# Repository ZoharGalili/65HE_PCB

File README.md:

# 65HE_PCB

this is a 65% hall effect keyboard pcb running [libhmk](https://github.com/peppapighs/libhmk) firmware.

## Board Renders

## Features

- all the usual features of an HE keyboard listed in the [libhmk](https://github.com/peppapighs/libhmk) repo.
- multilayout support (7u/6.25u spacebar, split backspace, stepped caps).
- bakeneko 65 combined with ai03 vega board outline supports gummy o-ring mount.
- at32f405 microcontroller enables 8khz polling rate.
- uses 4 of the ai03 vega outer plate screws.

## Layout

### big thanks to peppapighs 

I pretty much coppied the schematic design of the [HE60](https://github.com/peppapighs/HE60) xD

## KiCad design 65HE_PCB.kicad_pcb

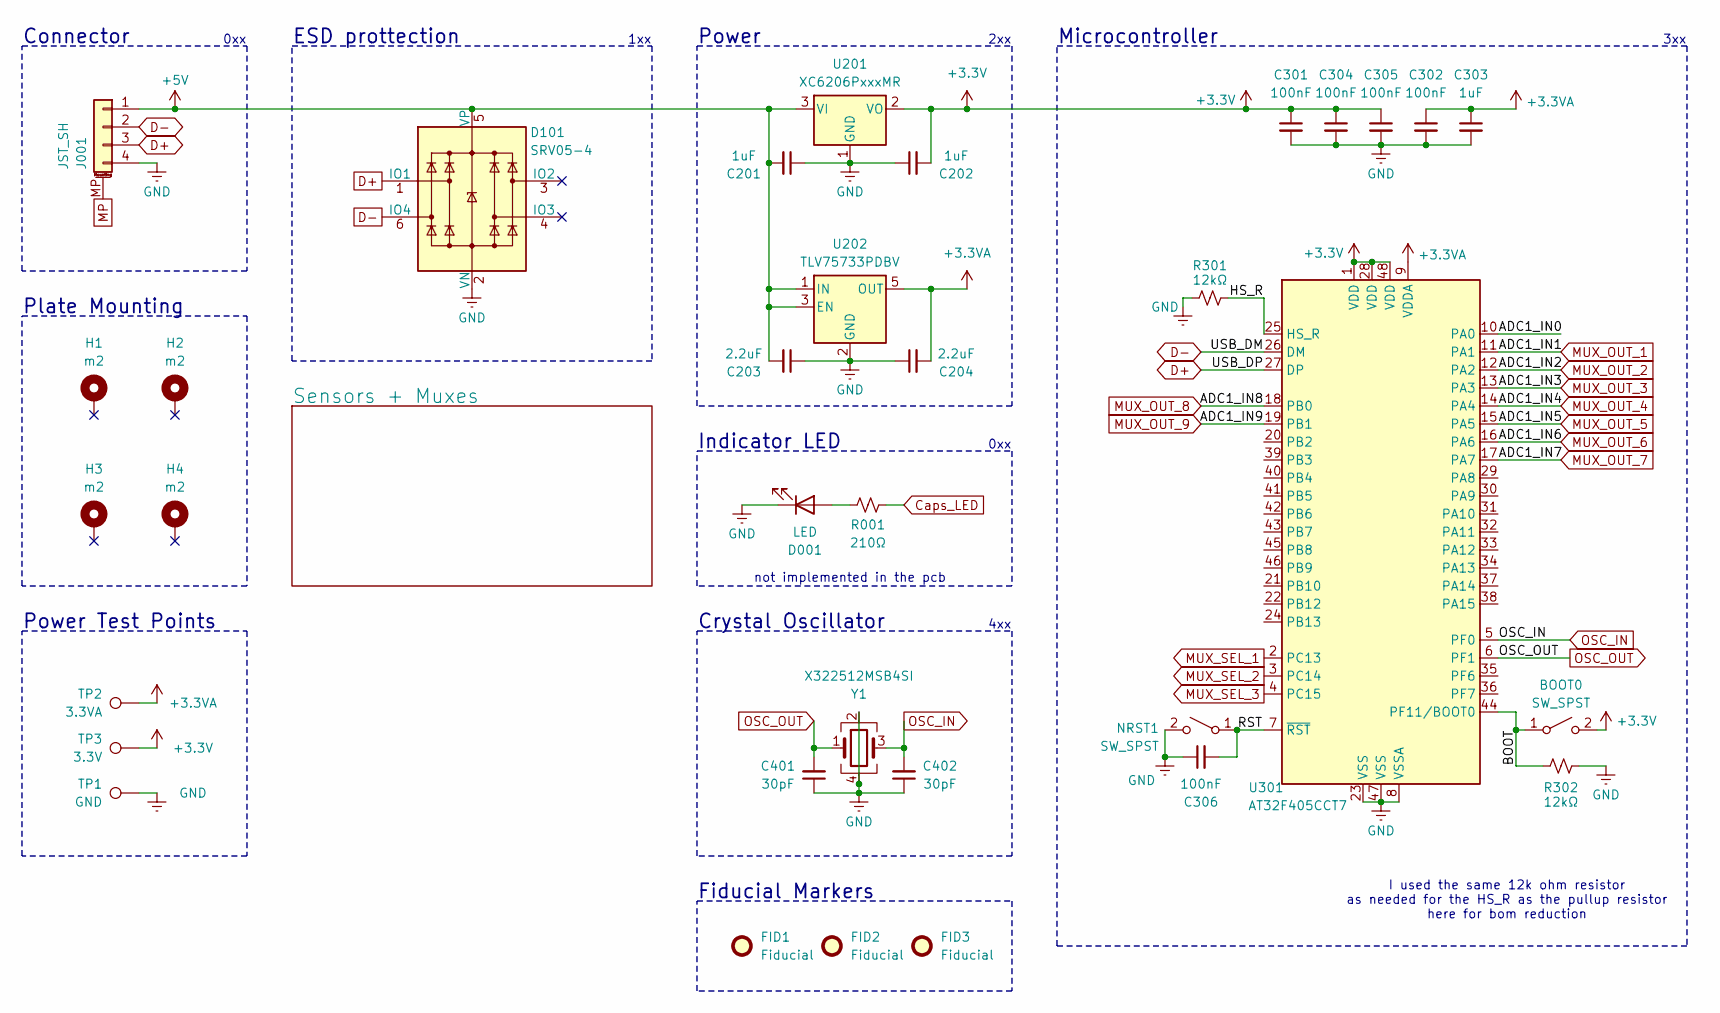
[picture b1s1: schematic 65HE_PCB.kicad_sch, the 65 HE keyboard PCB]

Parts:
BOOT0: SW_SPST; SW_SPST_SKQG_WithStem
C201, C202, C303: 1uF; C_1206_3216Metric
C203, C204: 2.2uF; C_1206_3216Metric
C301, C302, C304, C305, C306: 100nF; C_0805_2012Metric
C401, C402: 30pF; C_0603_1608Metric
D001: LED; LED_1206_3216Metric_ReverseMount_Hole1.8x2.4mm
D101: SRV05-4; SOT-23-6-routable
FID1, FID2, FID3: Fiducial; Fiducial_1mm_Mask2mm
H1, H2, H3, H4: m2; MountingHole_2.2mm_M2_Pad
J001: JST_SH; JST_SH_SM04B-SRSS-TB_1x04-1MP_P1.00mm_Horizontal
NRST1: SW_SPST; SW_SPST_SKQG_WithStem
R001: 210Ω; R_0805_2012Metric; LCSC C5357171
R301, R302: 12kΩ; R_0805_2012Metric
TP1: GND; TestPoint_Pad_2.0x2.0mm
TP2: 3.3VA; TestPoint_Pad_D2.0mm
TP3: 3.3V; TestPoint_Pad_D2.0mm
U201: XC6206PxxxMR; SOT-23-3
U202: TLV75733PDBV; SOT-23-5
U301: AT32F405CCT7; LQFP-48_7x7mm_P0.5mm
Y1: X322512MSB4SI; Crystal_SMD_3225-4Pin_3.2x2.5mm

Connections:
+3.3V: BOOT0.2 (B), C202.2, C301.1, C304.1, C305.1, TP3.1, U201.2 (VO), U301.1 (VDD), U301.28 (VDD), U301.48 (VDD)
+3.3VA: C204.2, C302.1, C303.1, TP2.1, U202.5 (OUT), U301.9 (VDDA); also elsewhere on the board
+5V: C201.2, C203.2, D101.5 (VP), J001.1, U201.3 (VI), U202.1 (IN), U202.3 (EN)
/ADC1_IN0: U301.10 (PA0)
/BOOT: BOOT0.1 (A), R302.2, U301.44 (PF11/BOOT0)
/HS_R: R301.1, U301.25 (HS_R)
/RST: C306.2, NRST1.1 (A), U301.7 (~RST)
D+: D101.1 (IO1), J001.3, U301.27 (DP)
D-: D101.6 (IO4), J001.2, U301.26 (DM)
GND: C201.1, C202.1, C203.1, C204.1, C301.2, C302.2, C303.2, C304.2, C305.2, C306.1, C401.1, C402.1, D001.1 (K), D101.2 (VN), J001.4, NRST1.2 (B), R301.2, R302.1, TP1.1, U201.1 (GND), U202.2 (GND), U301.8 (VSSA), U301.23 (VSS), U301.47 (VSS), Y1.2, Y1.4; also elsewhere on the board
MP: J001.MP (MountPin)
MUX_OUT_1: U301.11 (PA1); also elsewhere on the board
MUX_OUT_2: U301.12 (PA2); also elsewhere on the board
MUX_OUT_3: U301.13 (PA3); also elsewhere on the board
MUX_OUT_4: U301.14 (PA4); also elsewhere on the board
MUX_OUT_5: U301.15 (PA5); also elsewhere on the board
MUX_OUT_6: U301.16 (PA6); also elsewhere on the board
MUX_OUT_7: U301.17 (PA7); also elsewhere on the board
MUX_OUT_8: U301.18 (PB0); also elsewhere on the board
MUX_OUT_9: U301.19 (PB1); also elsewhere on the board
MUX_SEL_1: U301.2 (PC13); also elsewhere on the board
MUX_SEL_2: U301.3 (PC14); also elsewhere on the board
MUX_SEL_3: U301.4 (PC15); also elsewhere on the board
unnamed: D001.2 (A), R001.1
OSC_IN: C402.2, U301.5 (PF0), Y1.3
OSC_OUT: C401.2, U301.6 (PF1), Y1.1

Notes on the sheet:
Connector
Power Test Points
1xx
2xx
0xx
Plate Mounting
Fiducial Markers
ESD prottection
3xx
Power
not implemented in the pcb
Microcontroller
4xx
I used the same 12k ohm resistor as needed for the HS_R as the pullup resistor here for bom reduction
Indicator LED
Crystal Oscillator

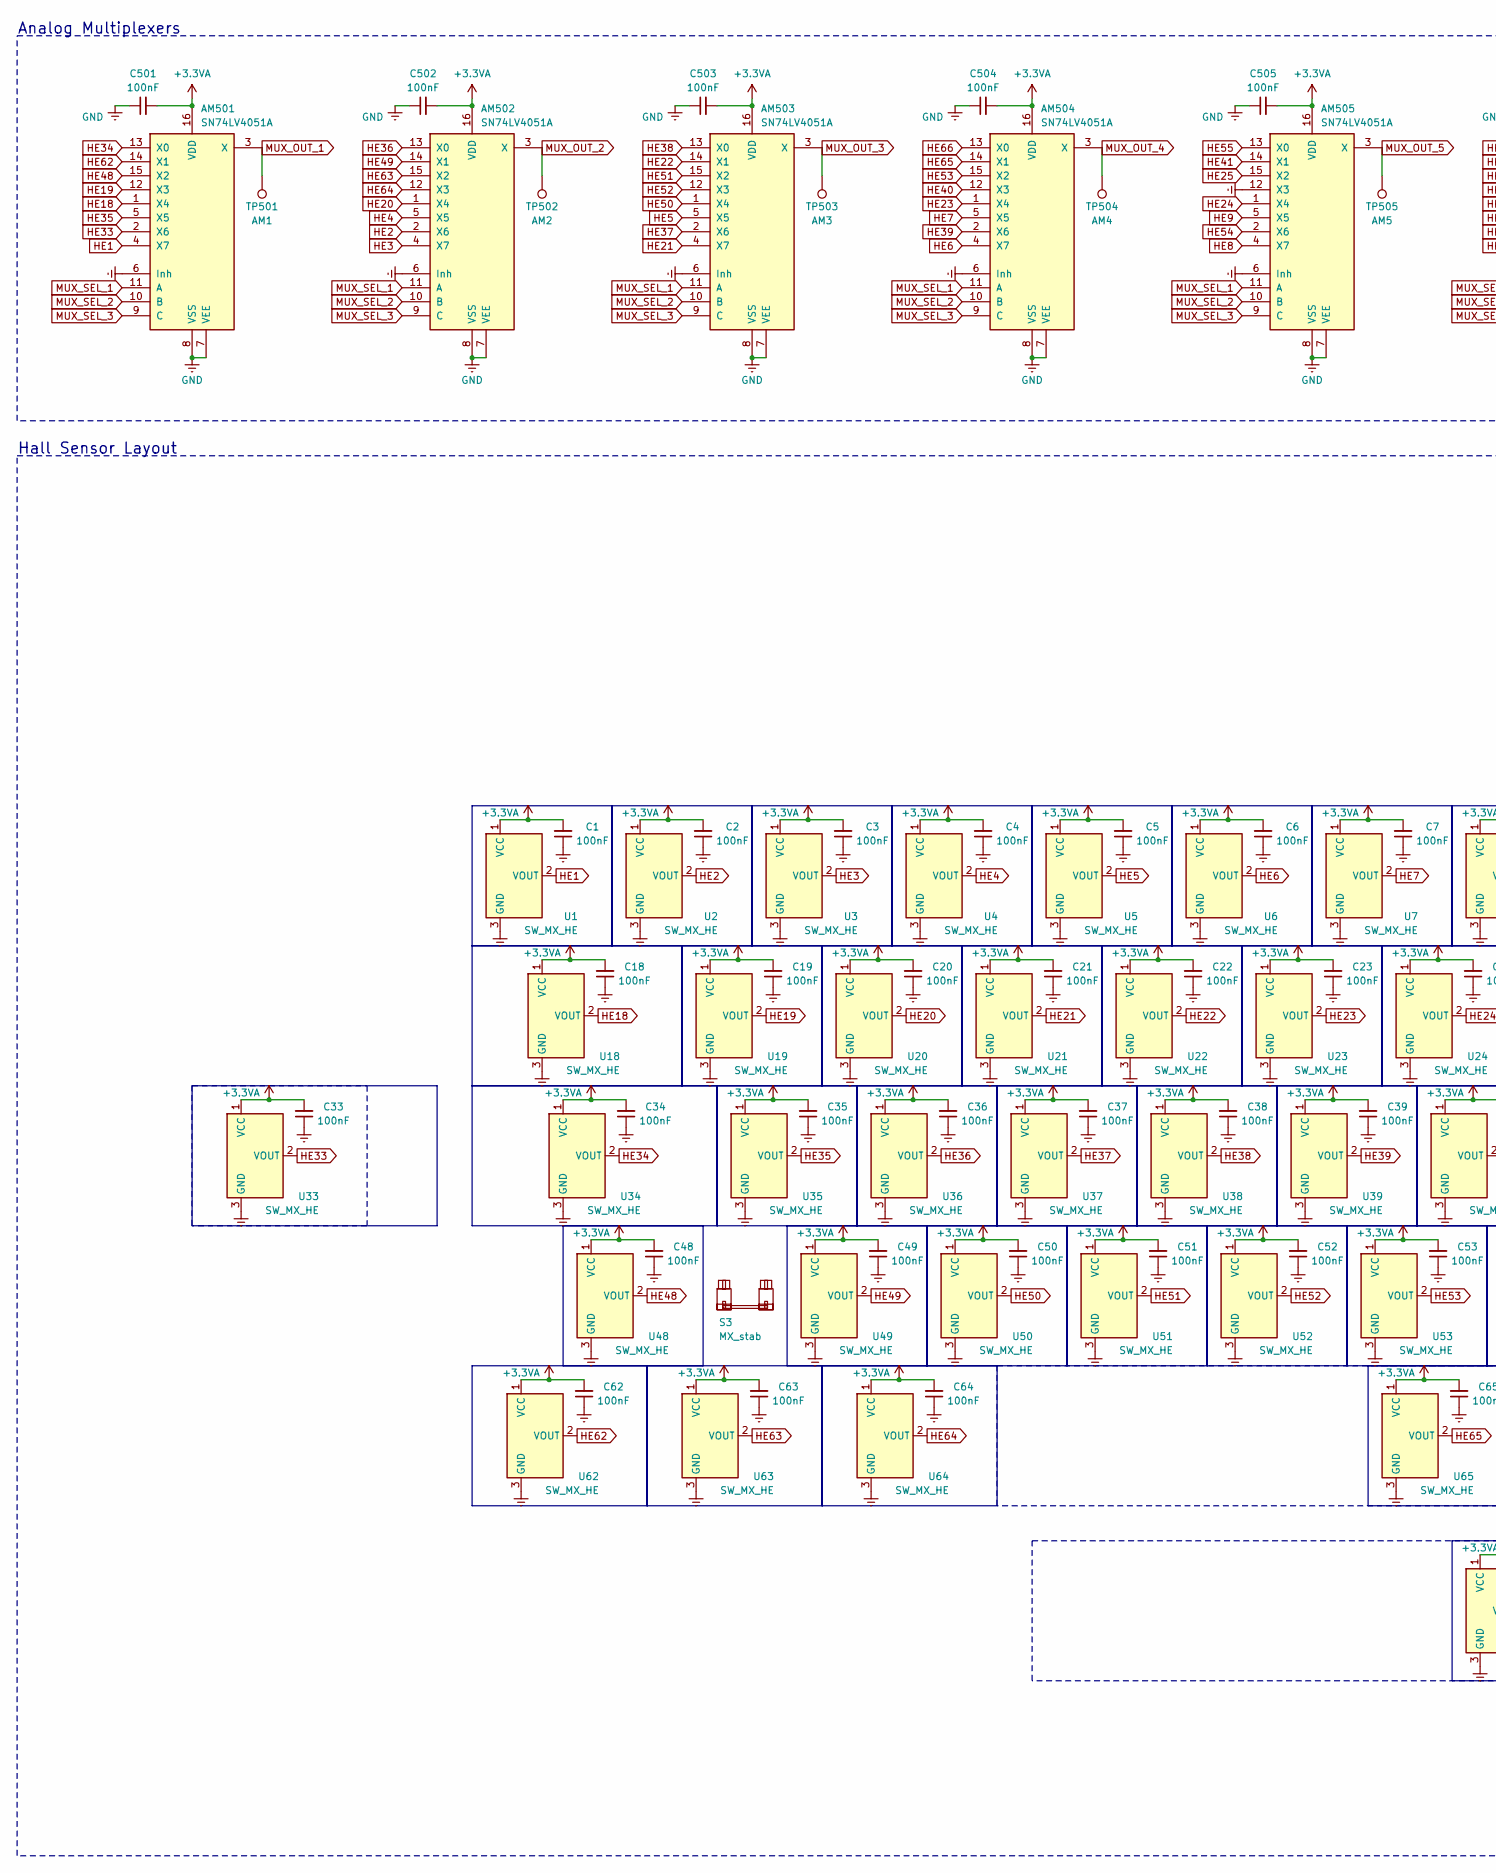
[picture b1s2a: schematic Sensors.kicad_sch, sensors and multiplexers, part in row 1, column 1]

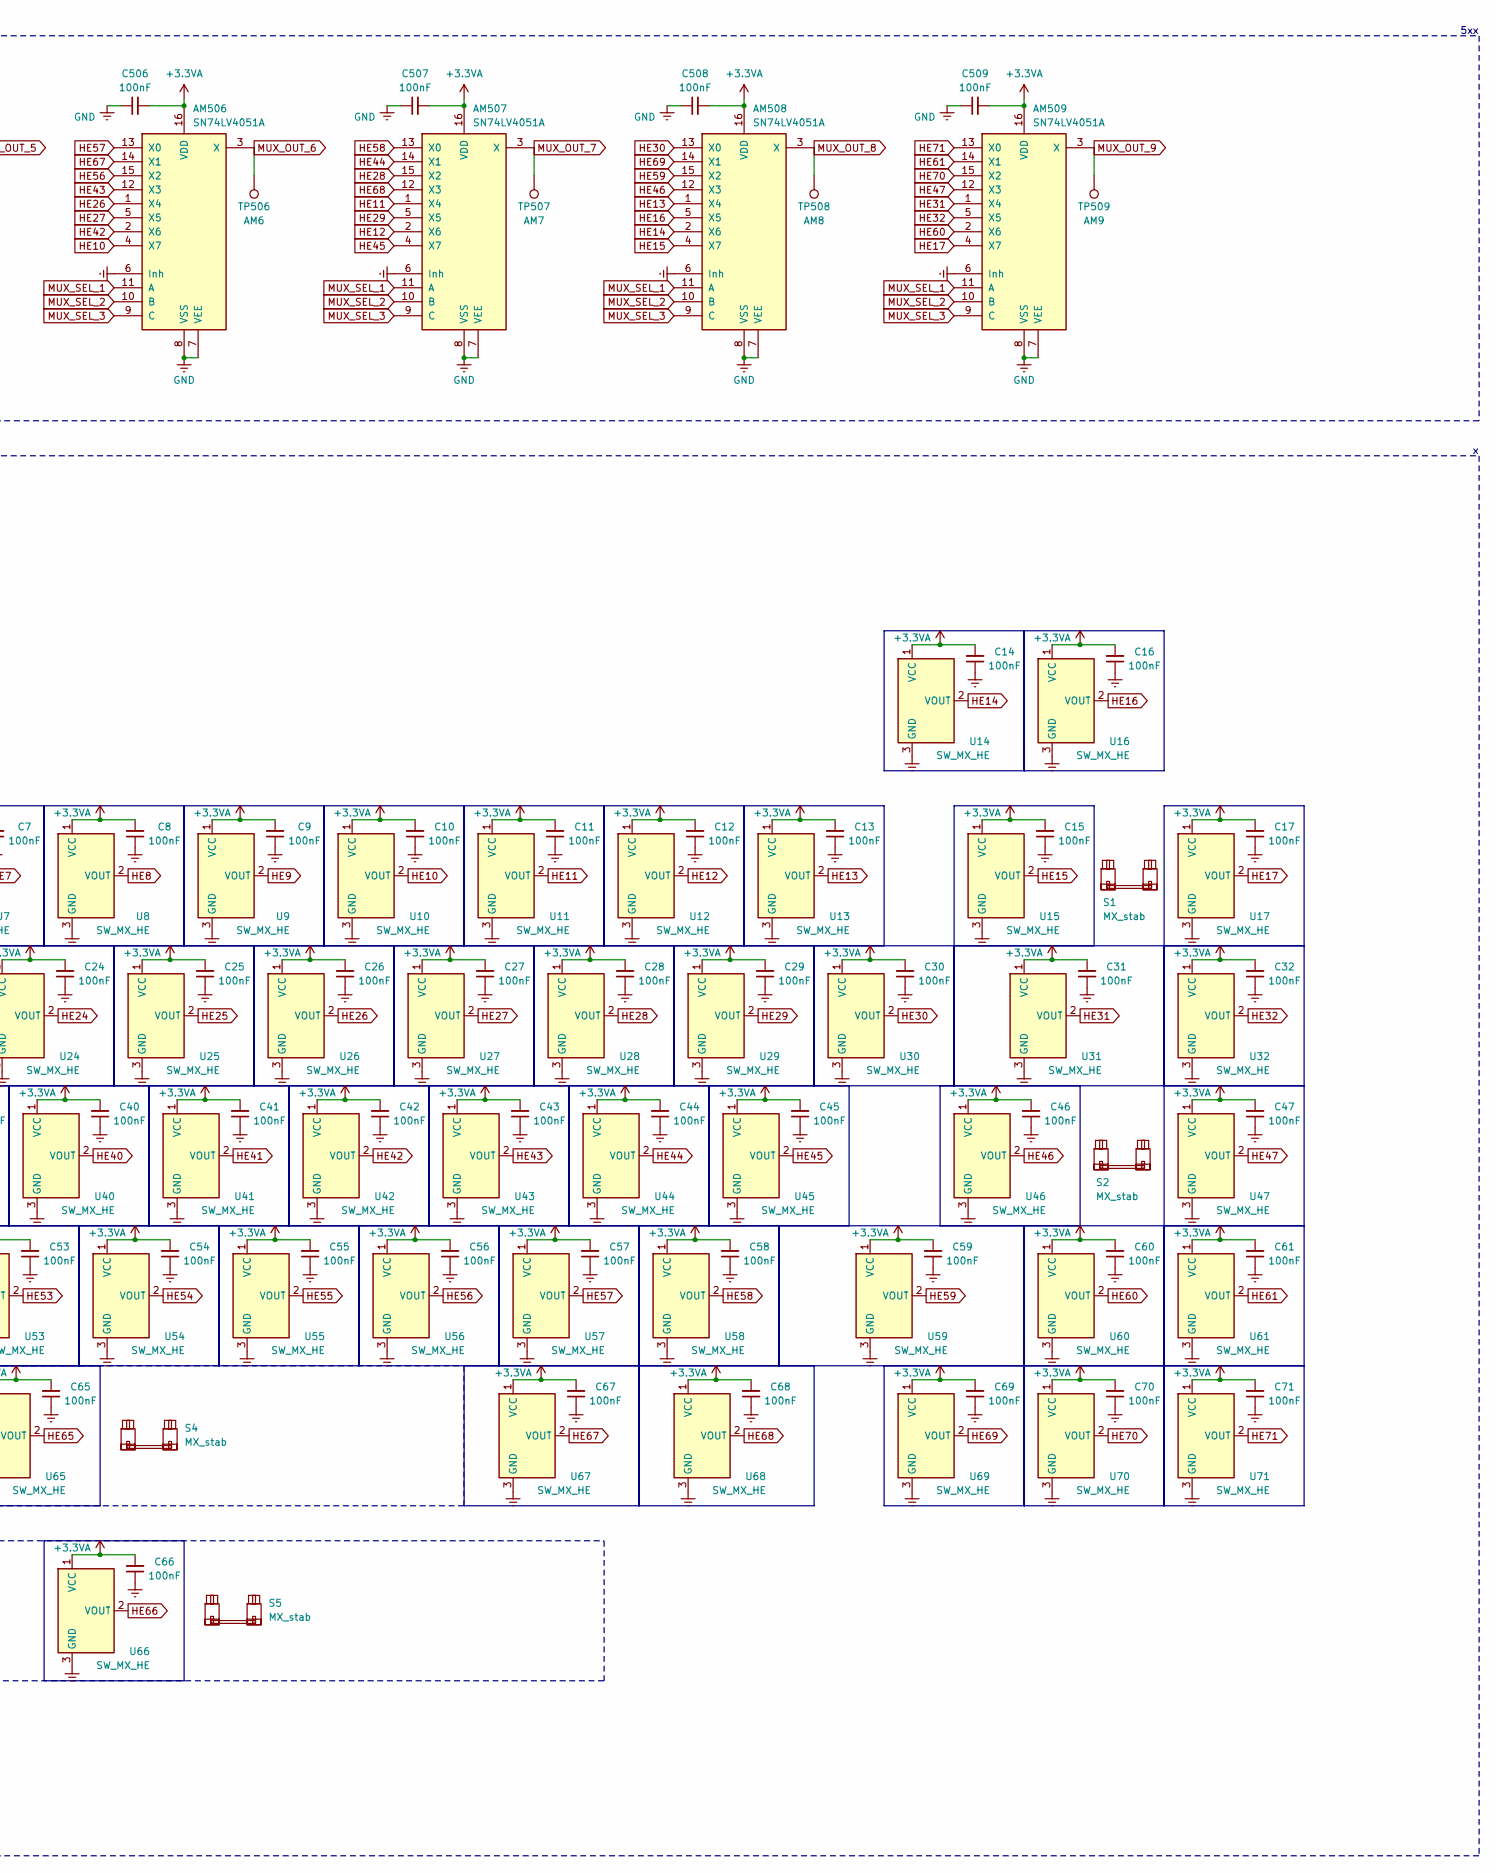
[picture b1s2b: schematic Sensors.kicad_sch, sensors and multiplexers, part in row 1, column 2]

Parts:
AM501, AM502, AM503, AM504, AM505, AM506, AM507, AM508, AM509: SN74LV4051A; TSSOP-16_4.4x5mm_P0.65mm
C1, C2, C3, C4, C5, C6, C7, C8, C9, C10, C11, C12, C13, C14, C15, C16, C17, C18, C19, C20, C21, C22, C23, C24, C25, C26, C27, C28, C29, C30, C31, C32, C33, C34, C35, C36, C37, C38, C39, C40, C41, C42, C43, C44, C45, C46, C47, C48, C49, C50, C51, C52, C53, C54, C55, C56, C57, C58, C59, C60, C61, C62, C63, C64, C65, C66, C67, C68, C69, C70, C71, C501, C502, C503, C504, C505, C506, C507, C508, C509: 100nF; C_0805_2012Metric
S1: MX_stab; STAB_MX_P_2u
S2, S3: MX_stab; STAB_MX_P_2.25u
S4: MX_stab; STAB_MX_P_6.25u
S5: MX_stab; STAB_MX_P_7u
TP501: AM1; TestPoint_Pad_D2.0mm
TP502: AM2; TestPoint_Pad_D2.0mm
TP503: AM3; TestPoint_Pad_D2.0mm
TP504: AM4; TestPoint_Pad_D2.0mm
TP505: AM5; TestPoint_Pad_D2.0mm
TP506: AM6; TestPoint_Pad_D2.0mm
TP507: AM7; TestPoint_Pad_D2.0mm
TP508: AM8; TestPoint_Pad_D2.0mm
TP509: AM9; TestPoint_Pad_D2.0mm
U1, U2, U3, U4, U5, U6, U7, U8, U9, U10, U11, U12, U13, U14, U15, U16, U17, U18, U19, U20, U21, U22, U23, U24, U25, U26, U27, U28, U29, U30, U31, U32, U34, U35, U36, U37, U38, U39, U40, U41, U42, U43, U44, U45, U46, U47, U48, U49, U50, U51, U52, U53, U54, U55, U56, U57, U58, U59, U60, U61, U65, U66, U67, U69, U70, U71: SW_MX_HE; SW_MX_HE_90deg_1u
U33: SW_MX_HE; SW_MX_HE_90deg_1.75u_STP_1.25
U62, U63, U64, U68: SW_MX_HE; SW_MX_HE_90deg_1_8u

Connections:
+3.3VA: AM501.16 (VDD), AM502.16 (VDD), AM503.16 (VDD), AM504.16 (VDD), AM505.16 (VDD), AM506.16 (VDD), AM507.16 (VDD), AM508.16 (VDD), AM509.16 (VDD), C1.2, C2.2, C3.2, C4.2, C5.2, C6.2, C7.2, C8.2, C9.2, C10.2, C11.2, C12.2, C13.2, C14.2, C15.2, C16.2, C17.2, C18.2, C19.2, C20.2, C21.2, C22.2, C23.2, C24.2, C25.2, C26.2, C27.2, C28.2, C29.2, C30.2, C31.2, C32.2, C33.2, C34.2, C35.2, C36.2, C37.2, C38.2, C39.2, C40.2, C41.2, C42.2, C43.2, C44.2, C45.2, C46.2, C47.2, C48.2, C49.2, C50.2, C51.2, C52.2, C53.2, C54.2, C55.2, C56.2, C57.2, C58.2, C59.2, C60.2, C61.2, C62.2, C63.2, C64.2, C65.2, C66.2, C67.2, C68.2, C69.2, C70.2, C71.2, C501.2, C502.2, C503.2, C504.2, C505.2, C506.2, C507.2, C508.2, C509.2, U1.1 (VCC), U2.1 (VCC), U3.1 (VCC), U4.1 (VCC), U5.1 (VCC), U6.1 (VCC), U7.1 (VCC), U8.1 (VCC), U9.1 (VCC), U10.1 (VCC), U11.1 (VCC), U12.1 (VCC), U13.1 (VCC), U14.1 (VCC), U15.1 (VCC), U16.1 (VCC), U17.1 (VCC), U18.1 (VCC), U19.1 (VCC), U20.1 (VCC), U21.1 (VCC), U22.1 (VCC), U23.1 (VCC), U24.1 (VCC), U25.1 (VCC), U26.1 (VCC), U27.1 (VCC), U28.1 (VCC), U29.1 (VCC), U30.1 (VCC), U31.1 (VCC), U32.1 (VCC), U33.1 (VCC), U34.1 (VCC), U35.1 (VCC), U36.1 (VCC), U37.1 (VCC), U38.1 (VCC), U39.1 (VCC), U40.1 (VCC), U41.1 (VCC), U42.1 (VCC), U43.1 (VCC), U44.1 (VCC), U45.1 (VCC), U46.1 (VCC), U47.1 (VCC), U48.1 (VCC), U49.1 (VCC), U50.1 (VCC), U51.1 (VCC), U52.1 (VCC), U53.1 (VCC), U54.1 (VCC), U55.1 (VCC), U56.1 (VCC), U57.1 (VCC), U58.1 (VCC), U59.1 (VCC), U60.1 (VCC), U61.1 (VCC), U62.1 (VCC), U63.1 (VCC), U64.1 (VCC), U65.1 (VCC), U66.1 (VCC), U67.1 (VCC), U68.1 (VCC), U69.1 (VCC), U70.1 (VCC), U71.1 (VCC); also elsewhere on the board
GND: AM501.6 (Inh), AM501.7 (VEE), AM501.8 (VSS), AM502.6 (Inh), AM502.7 (VEE), AM502.8 (VSS), AM503.6 (Inh), AM503.7 (VEE), AM503.8 (VSS), AM504.6 (Inh), AM504.7 (VEE), AM504.8 (VSS), AM505.6 (Inh), AM505.7 (VEE), AM505.8 (VSS), AM505.12 (X3), AM506.6 (Inh), AM506.7 (VEE), AM506.8 (VSS), AM507.6 (Inh), AM507.7 (VEE), AM507.8 (VSS), AM508.6 (Inh), AM508.7 (VEE), AM508.8 (VSS), AM509.6 (Inh), AM509.7 (VEE), AM509.8 (VSS), C1.1, C2.1, C3.1, C4.1, C5.1, C6.1, C7.1, C8.1, C9.1, C10.1, C11.1, C12.1, C13.1, C14.1, C15.1, C16.1, C17.1, C18.1, C19.1, C20.1, C21.1, C22.1, C23.1, C24.1, C25.1, C26.1, C27.1, C28.1, C29.1, C30.1, C31.1, C32.1, C33.1, C34.1, C35.1, C36.1, C37.1, C38.1, C39.1, C40.1, C41.1, C42.1, C43.1, C44.1, C45.1, C46.1, C47.1, C48.1, C49.1, C50.1, C51.1, C52.1, C53.1, C54.1, C55.1, C56.1, C57.1, C58.1, C59.1, C60.1, C61.1, C62.1, C63.1, C64.1, C65.1, C66.1, C67.1, C68.1, C69.1, C70.1, C71.1, C501.1, C502.1, C503.1, C504.1, C505.1, C506.1, C507.1, C508.1, C509.1, U1.3 (GND), U2.3 (GND), U3.3 (GND), U4.3 (GND), U5.3 (GND), U6.3 (GND), U7.3 (GND), U8.3 (GND), U9.3 (GND), U10.3 (GND), U11.3 (GND), U12.3 (GND), U13.3 (GND), U14.3 (GND), U15.3 (GND), U16.3 (GND), U17.3 (GND), U18.3 (GND), U19.3 (GND), U20.3 (GND), U21.3 (GND), U22.3 (GND), U23.3 (GND), U24.3 (GND), U25.3 (GND), U26.3 (GND), U27.3 (GND), U28.3 (GND), U29.3 (GND), U30.3 (GND), U31.3 (GND), U32.3 (GND), U33.3 (GND), U34.3 (GND), U35.3 (GND), U36.3 (GND), U37.3 (GND), U38.3 (GND), U39.3 (GND), U40.3 (GND), U41.3 (GND), U42.3 (GND), U43.3 (GND), U44.3 (GND), U45.3 (GND), U46.3 (GND), U47.3 (GND), U48.3 (GND), U49.3 (GND), U50.3 (GND), U51.3 (GND), U52.3 (GND), U53.3 (GND), U54.3 (GND), U55.3 (GND), U56.3 (GND), U57.3 (GND), U58.3 (GND), U59.3 (GND), U60.3 (GND), U61.3 (GND), U62.3 (GND), U63.3 (GND), U64.3 (GND), U65.3 (GND), U66.3 (GND), U67.3 (GND), U68.3 (GND), U69.3 (GND), U70.3 (GND), U71.3 (GND); also elsewhere on the board
HE1: AM501.4 (X7), U1.2 (VOUT)
HE2: AM502.2 (X6), U2.2 (VOUT)
HE3: AM502.4 (X7), U3.2 (VOUT)
HE4: AM502.5 (X5), U4.2 (VOUT)
HE5: AM503.5 (X5), U5.2 (VOUT)
HE6: AM504.4 (X7), U6.2 (VOUT)
HE7: AM504.5 (X5), U7.2 (VOUT)
HE8: AM505.4 (X7), U8.2 (VOUT)
HE9: AM505.5 (X5), U9.2 (VOUT)
HE10: AM506.4 (X7), U10.2 (VOUT)
HE11: AM507.1 (X4), U11.2 (VOUT)
HE12: AM507.2 (X6), U12.2 (VOUT)
HE13: AM508.1 (X4), U13.2 (VOUT)
HE14: AM508.2 (X6), U14.2 (VOUT)
HE15: AM508.4 (X7), U15.2 (VOUT)
HE16: AM508.5 (X5), U16.2 (VOUT)
HE17: AM509.4 (X7), U17.2 (VOUT)
HE18: AM501.1 (X4), U18.2 (VOUT)
HE19: AM501.12 (X3), U19.2 (VOUT)
HE20: AM502.1 (X4), U20.2 (VOUT)
HE21: AM503.4 (X7), U21.2 (VOUT)
HE22: AM503.14 (X1), U22.2 (VOUT)
HE23: AM504.1 (X4), U23.2 (VOUT)
HE24: AM505.1 (X4), U24.2 (VOUT)
HE25: AM505.15 (X2), U25.2 (VOUT)
HE26: AM506.1 (X4), U26.2 (VOUT)
HE27: AM506.5 (X5), U27.2 (VOUT)
HE28: AM507.15 (X2), U28.2 (VOUT)
HE29: AM507.5 (X5), U29.2 (VOUT)
HE30: AM508.13 (X0), U30.2 (VOUT)
HE31: AM509.1 (X4), U31.2 (VOUT)
HE32: AM509.5 (X5), U32.2 (VOUT)
HE33: AM501.2 (X6), U33.2 (VOUT)
HE34: AM501.13 (X0), U34.2 (VOUT)
HE35: AM501.5 (X5), U35.2 (VOUT)
HE36: AM502.13 (X0), U36.2 (VOUT)
HE37: AM503.2 (X6), U37.2 (VOUT)
HE38: AM503.13 (X0), U38.2 (VOUT)
HE39: AM504.2 (X6), U39.2 (VOUT)
HE40: AM504.12 (X3), U40.2 (VOUT)
HE41: AM505.14 (X1), U41.2 (VOUT)
HE42: AM506.2 (X6), U42.2 (VOUT)
HE43: AM506.12 (X3), U43.2 (VOUT)
HE44: AM507.14 (X1), U44.2 (VOUT)
HE45: AM507.4 (X7), U45.2 (VOUT)
HE46: AM508.12 (X3), U46.2 (VOUT)
HE47: AM509.12 (X3), U47.2 (VOUT)
HE48: AM501.15 (X2), U48.2 (VOUT)
HE49: AM502.14 (X1), U49.2 (VOUT)
HE50: AM503.1 (X4), U50.2 (VOUT)
HE51: AM503.15 (X2), U51.2 (VOUT)
HE52: AM503.12 (X3), U52.2 (VOUT)
HE53: AM504.15 (X2), U53.2 (VOUT)
HE54: AM505.2 (X6), U54.2 (VOUT)
HE55: AM505.13 (X0), U55.2 (VOUT)
HE56: AM506.15 (X2), U56.2 (VOUT)
HE57: AM506.13 (X0), U57.2 (VOUT)
HE58: AM507.13 (X0), U58.2 (VOUT)
HE59: AM508.15 (X2), U59.2 (VOUT)
HE60: AM509.2 (X6), U60.2 (VOUT)
HE61: AM509.14 (X1), U61.2 (VOUT)
HE62: AM501.14 (X1), U62.2 (VOUT)
HE63: AM502.15 (X2), U63.2 (VOUT)
HE64: AM502.12 (X3), U64.2 (VOUT)
HE65: AM504.14 (X1), U65.2 (VOUT)
HE66: AM504.13 (X0), U66.2 (VOUT)
HE67: AM506.14 (X1), U67.2 (VOUT)
HE68: AM507.12 (X3), U68.2 (VOUT)
HE69: AM508.14 (X1), U69.2 (VOUT)
HE70: AM509.15 (X2), U70.2 (VOUT)
HE71: AM509.13 (X0), U71.2 (VOUT)
MUX_OUT_1: AM501.3 (X), TP501.1; also elsewhere on the board
MUX_OUT_2: AM502.3 (X), TP502.1; also elsewhere on the board
MUX_OUT_3: AM503.3 (X), TP503.1; also elsewhere on the board
MUX_OUT_4: AM504.3 (X), TP504.1; also elsewhere on the board
MUX_OUT_5: AM505.3 (X), TP505.1; also elsewhere on the board
MUX_OUT_6: AM506.3 (X), TP506.1; also elsewhere on the board
MUX_OUT_7: AM507.3 (X), TP507.1; also elsewhere on the board
MUX_OUT_8: AM508.3 (X), TP508.1; also elsewhere on the board
MUX_OUT_9: AM509.3 (X), TP509.1; also elsewhere on the board
MUX_SEL_1: AM501.11 (A), AM502.11 (A), AM503.11 (A), AM504.11 (A), AM505.11 (A), AM506.11 (A), AM507.11 (A), AM508.11 (A), AM509.11 (A); also elsewhere on the board
MUX_SEL_2: AM501.10 (B), AM502.10 (B), AM503.10 (B), AM504.10 (B), AM505.10 (B), AM506.10 (B), AM507.10 (B), AM508.10 (B), AM509.10 (B); also elsewhere on the board
MUX_SEL_3: AM501.9 (C), AM502.9 (C), AM503.9 (C), AM504.9 (C), AM505.9 (C), AM506.9 (C), AM507.9 (C), AM508.9 (C), AM509.9 (C); also elsewhere on the board

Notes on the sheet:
5xx
Analog Multiplexers
Hall Sensor Layout

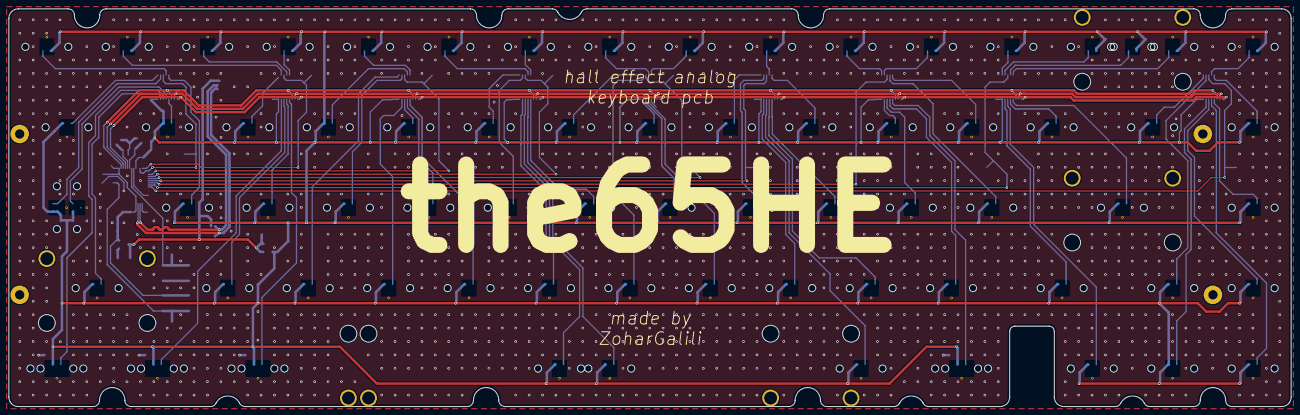
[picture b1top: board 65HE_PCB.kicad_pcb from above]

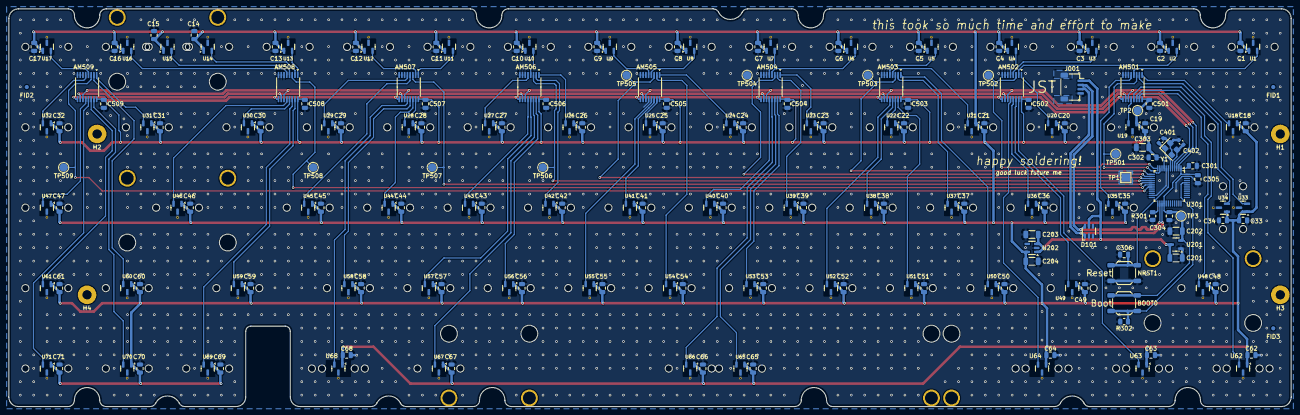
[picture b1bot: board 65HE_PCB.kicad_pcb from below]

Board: 2 copper layers, 303.8 x 94.2 mm, 206 parts (201 on the bottom side), 94 nets.

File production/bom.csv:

Designator,Footprint,Quantity,Value,LCSC Part #
"AM501, AM502, AM503, AM504, AM505, AM506, AM507, AM508, AM509, AM510",TSSOP-16_4.4x5mm_P0.65mm,10,SN74LV4051A,C7793
"BOOT0, NRST1",SW_SPST_SKQG_WithStem 5.1 x 5.1 MM,2,SW_SPST,C318884
"C1, C10, C11, C12, C13, C14, C15, C16, C17, C18, C19, C2, C20, C21, C22, C23, C24, C25, C26, C27, C28, C29, C3, C30, C301, C302, C304, C305, C306, C31, C32, C33, C34, C35, C36, C37, C38, C39, C4, C40, C41, C42, C43, C44, C45, C46, C47, C48, C49, C5, C50, C501, C502, C503, C504, C505, C506, C507, C508, C509, C51, C510, C52, C53, C54, C55, C56, C57, C58, C59, C6, C60, C61, C62, C63, C64, C65, C66, C67, C68, C69, C7, C70, C71, C72, C73, C74, C75, C8, C9",805,90,100nF,C5137467
"C201, C202, C303",1206,3,1uF,C1848
"C203, C204",1206,2,2.2uF,C50254
"C401, C402",603,2,30pF,C113797
D101,SOT-23-6-routable,1,SRV05-4,C2836319
J001,JST_SH_SM04B-SRSS-TB_1x04-1MP_P1.00mm_Horizontal,1,WAFER-SH1.0-4PWB,C3029343
"R301, R302",805,2,12kΩ,C114556
"U1, U10, U11, U12, U13, U14, U15, U16, U17, U18, U19, U2, U20, U21, U22, U23, U24, U25, U26, U27, U28, U29, U3, U30, U31, U32, U33, U34, U35, U36, U37, U38, U39, U4, U40, U41, U42, U43, U44, U45, U46, U47, U48, U49, U5, U50, U51, U52, U53, U54, U55, U56, U57, U58, U59, U6, U60, U61, U63, U65, U67, U68, U69, U7, U70, U72, U73, U74, U75, U8, U9, U62, U64, U66, U71",SW_MX_HE_90deg_1u,71,SW_MX_HE,C7420984
U201,SOT-23-3,1,XC6206PxxxMR,C347376
U202,SOT-23-5,1,TLV75733PDBV,C485517
U301,LQFP-48_7x7mm_P0.5mm,1,AT32F405CCT7,C47115471
Y1,Crystal_SMD_3225-4Pin_3.2x2.5mm,1,X322512MSB4SI,C9002

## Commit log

2025-10-04 initial commit
    i made the board yay!
2025-10-06 no rounded tracks
    routed the pcb again but without rounding the tracks because kicad became laggy af
2025-10-10 full PCB and BOM
    the pcb is done (i hope) and i made the production files and filled out the bom with parts from lcsc
2025-11-14 1 less multiplexer!
    made the whole board again to use only 1 sensor for each 1/8 unit pair of switches on the bottom row. i also made some improvements in the whole design itself
2025-11-14 Add initial README
2025-11-15 polished up the board and readme
    added silckscreen to the board and filled out the readme with some basic information
2025-11-15 hopefully fixed the readme
2025-11-18 added test points
    added test points to the pcb power lines and multiplexer outputs, hopefully the readme is fixed as well
2025-11-18 temp folder name
2025-11-18 all good now?
